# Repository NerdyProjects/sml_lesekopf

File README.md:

# sml_lesekopf

This project implements the SML infrared read/write interface from [Volkszaehler](https://wiki.volkszaehler.org/hardware/controllers/ir-schreib-lesekopf-ttl-ausgang) and adds generic RS422/RS485 capabilities.

The PCB is of 27mm diameter and meant to be used with a 27/16/5mm magnet.

## Building

The PCB can be used in different operating modes. Each of those can be used independently, just add all the variants together you want to have

### Basic (reverse polarity protection)
* D2: Any SMA (or smaller) shottky diode (e.g. BAT46); if in doubt, also a silicon diode like 1N4148 is appropriate but has higher voltage drop

### Infrared receiver
To read out smartmeters that send data themselves, you only need the infrared receiver part consisting of:
* C1: 1µF 0805 ceramic capacitor
* R2: 13k Ohms 0805 resistor
* R4: 13k Ohms 0805 resistor
* Q3: Any SOT23 NPN transistor, e.g. BC817
* Q2: SFH309 FA infrared phototransistor (860nm). If in doubt, take the -4 version.
* U2: 74LVC1G17 schmitt trigger buffer (can be omitted when the device has schmitt trigger inputs and you use short cables; bridge pins 2 and 4 in that case)

This outputs the received signal as a TTL signal on the TX pin. Feel free to use any supply voltage between 2 and 5.5V, your output signal will have the same voltage levels.

### Infrared transmitter
Some smartmeters require a signal sent to them to start transmitting data, so you need transmission capabilities:
* C2: 1µF 0805 ceramic capacitor
* R1: 180 Ohms 0805 resistor
* D1: SFH487 or any other ~860 nm infrared LED with a viewing angle of 30..60 degrees (e.g. Reichelt L-7104SF4BT KB)
* Q1: Any SOT23 PNP transistor, e.g. BC807
* R3: 13k Ohms 0805 resisotr
* U1: 74LVC1G17 schmitt trigger buffer (can be omitted when you use short cables, bridge pins 2 and 4 in that case)

Alternatively, you can use a 74LVC1G14 (Inverter) and leave out R3/Q1 (bridging R3 and bridging pins 1 and 3 of Q1)

### RS485/RS422 infrared receiver/bus transmitter only (single device on the bus)
To transmit the signal over wires longer than a few metres (up to 200m or even further), you can put a RS422/RS485 bus transceiver for U3.
There is many options regarding your supply voltage and the bus voltage levels. In any case, you also need to supply C3.
A transceiver with a lower maximum data rate has better EMI performance as well as better performance with long, unterminated bus wires (e.g. the SP3072E)
Use the A/B connection for data transfer, RX/TX stay unconnected in this case.
* C3: 1µF 0805 ceramic capacitor
* U3: SN75176BD (5V, ~50mA standby current); SP485CNL(5V, low power); ADM485 (5V, 2 mA standby current); MAX485CSA (5V, low power); SP3072E(3,3V, <2 mA)

### RS422 bidirectional
RS422/RS485 full duplex interfaces transmit and receive at the same time. You need to connect 2 wires for TX/RX each and the supply voltage.
* C4: 1µF 0805 ceramic capacitor
* U4: DS89C21(5V, <10 mA); SP3071E(3,3V, <2 mA)

### RS485 auto direction
A MAX22025 auto direction RS485 transceiver can be used to use a half duplex, bidirectional RS485 transfer using only 4 wires in total.
Change both solder jumpers JP1 and JP2 on the top side of the PCB.

### RS485/RS422 PC interface
By changing the solder jumper JP3 (on the back side of the PCB), the half duplex RS485 transceiver U3 is put into receive mode.
Placing the components D2, C3 and U3 allows the PCB to be used as a TTL to RS485 (receive only) interface.
Input pin "RX/J3/DI" of the TTL side is then used as the TTL TX pin towards a computer or another device.

## Case
In the 3d folder, there is a printable case where you can put the magnet and the PCB in. The PCBs might fight very tightly, I suggest printing it at 102% scale.

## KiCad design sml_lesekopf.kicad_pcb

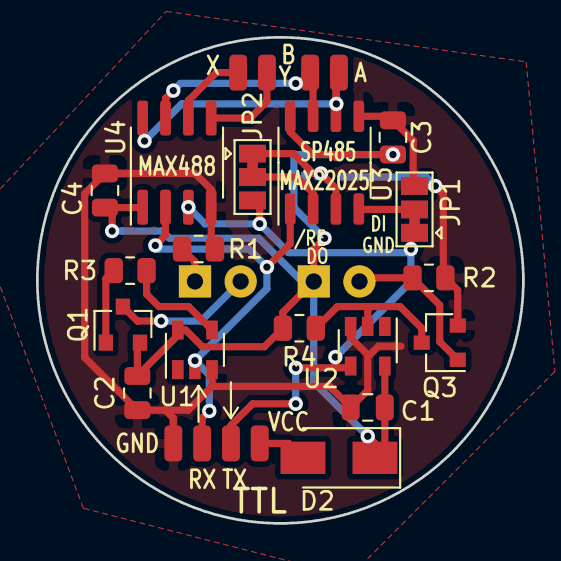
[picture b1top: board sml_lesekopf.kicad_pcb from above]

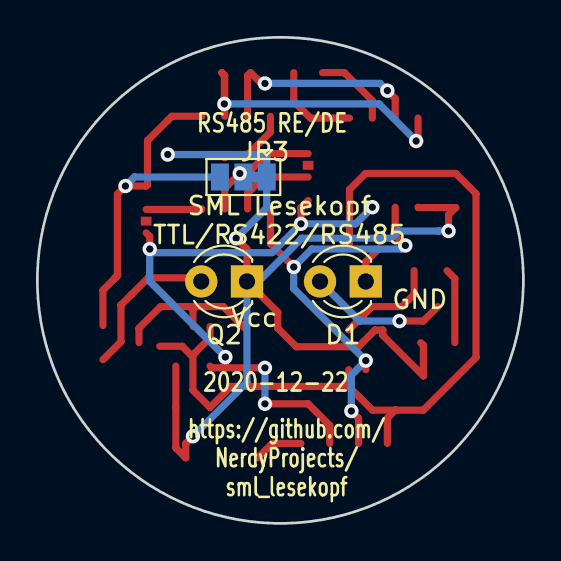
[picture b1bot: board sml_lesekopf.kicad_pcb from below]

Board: 2 copper layers, 27.0 x 27.0 mm, 28 parts (3 on the bottom side), 18 nets.

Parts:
C1, C2, C3, C4: 1µ; C_0805_2012Metric
D1: SFH482; LED_D3.0mm_IRGrey
D2: BAT46; D_SMA
J1: +Ub; SolderWirePad_1x01_SMD_1x2mm
J2: GND; SolderWirePad_1x01_SMD_1x2mm
J3: TTL_IN; SolderWirePad_1x01_SMD_1x2mm
J4: TTL_OUT; SolderWirePad_1x01_SMD_1x2mm
J5: B; SolderWirePad_1x01_SMD_1x2mm
J6: A; SolderWirePad_1x01_SMD_1x2mm
J7: Z; SolderWirePad_1x01_SMD_1x2mm
J8: Y; SolderWirePad_1x01_SMD_1x2mm
JP1, JP2, JP3: SolderJumper_3_Bridged12; SolderJumper-3_P1.3mm_Bridged12_Pad1.0x1.5mm
Q1: BC807; SOT-23
Q2: SFH309; LED_D3.0mm_Clear
Q3: BC817; SOT-23
R1: 180; R_0805_2012Metric
R2, R3, R4: 13k; R_0805_2012Metric
U1, U2: 74LVC1G17; SOT-23-5
U3: MAX485E; SO-8_3.9x4.9mm_P1.27mm
U4: ADM3490ExR; SOIC-8_3.9x4.9mm_P1.27mm

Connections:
DI: J3.1, U1.2, U3.1, U4.2
DO: J4.1, JP1.1, JP2.3, U2.4, U4.3
GND: C1.2, C2.2, C3.2, C4.2, J2.1, JP1.3, JP3.3, Q3.2, R1.1, R2.2, U1.3, U2.3, U3.5, U4.4
unnamed: D1.1, R1.2
unnamed: D1.2, Q1.3
unnamed: D2.2, J1.1
unnamed: J5.1, U3.7, U4.7
unnamed: J6.1, U3.6, U4.8
unnamed: J7.1, U4.6
unnamed: J8.1, U4.5
unnamed: JP1.2, U3.4
unnamed: JP2.1, JP3.2, U3.3
unnamed: JP2.2, U3.2
unnamed: Q1.1, R3.2
unnamed: Q2.2, Q3.1, R2.1
unnamed: Q3.3, R4.2, U2.2
unnamed: R3.1, U1.4
VCC: C1.1, C2.1, C3.1, C4.1, D2.1, JP3.1, Q1.2, Q2.1, R4.1, U1.5, U2.5, U3.8, U4.1

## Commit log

2020-12-22 add PCB
2020-12-22 readme draft
2020-12-22 update pcb
2020-12-22 update silkscreen
2020-12-22 add images of pcb
2020-12-22 Readme & pictures
2020-12-24 update IR led
2020-12-28 add 3d models
